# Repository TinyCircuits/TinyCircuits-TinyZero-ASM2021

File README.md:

# TinyCircuits TinyZero Processor Board
# ASM2021 Rev5

These are the design files for the TinyCircuits ASM2021 Rev 5 PCB.  This is a Tiny processor board (Square Version, 20mm x 20mm) that uses the same microcontroller (Atmel ATSAMD21G18A) as the Arduino Zero and has stackable TinyShield support.  

Format is in Cadsoft Eagle format - Eagle version 6.2 was used for the original design.

For more infomation on this, check out the product page at TinyCircuits.com:  https://tinycircuits.com/products/tinyzero-processor

# License:

Design by TinyCircuits.
All design files are released under the Creative Commons Attribution Share-Alike 3.0 License, see the following link for details: http://creativecommons.org/licenses/by-sa/3.0

All text above must be included in any redistribution or derived design

This project uses designs and concepts developed as part of the Arduino project and the LilyPad project.  The TinyCircuits design files themselves (schematics, PCB and libraries) are not directly derived from these works' design files and have been created new, however the concepts and basic architecture behind the TinyDuino and TinyLily products are derived and we thank the hard work of the organizations below for their contributions to open-source hardware:
  
Original Arduino Uno Design by Team Arduino

LilyPad Arduino Design by Leah Buechley and Sparkfun Electronics

Please support the open-source hardware community

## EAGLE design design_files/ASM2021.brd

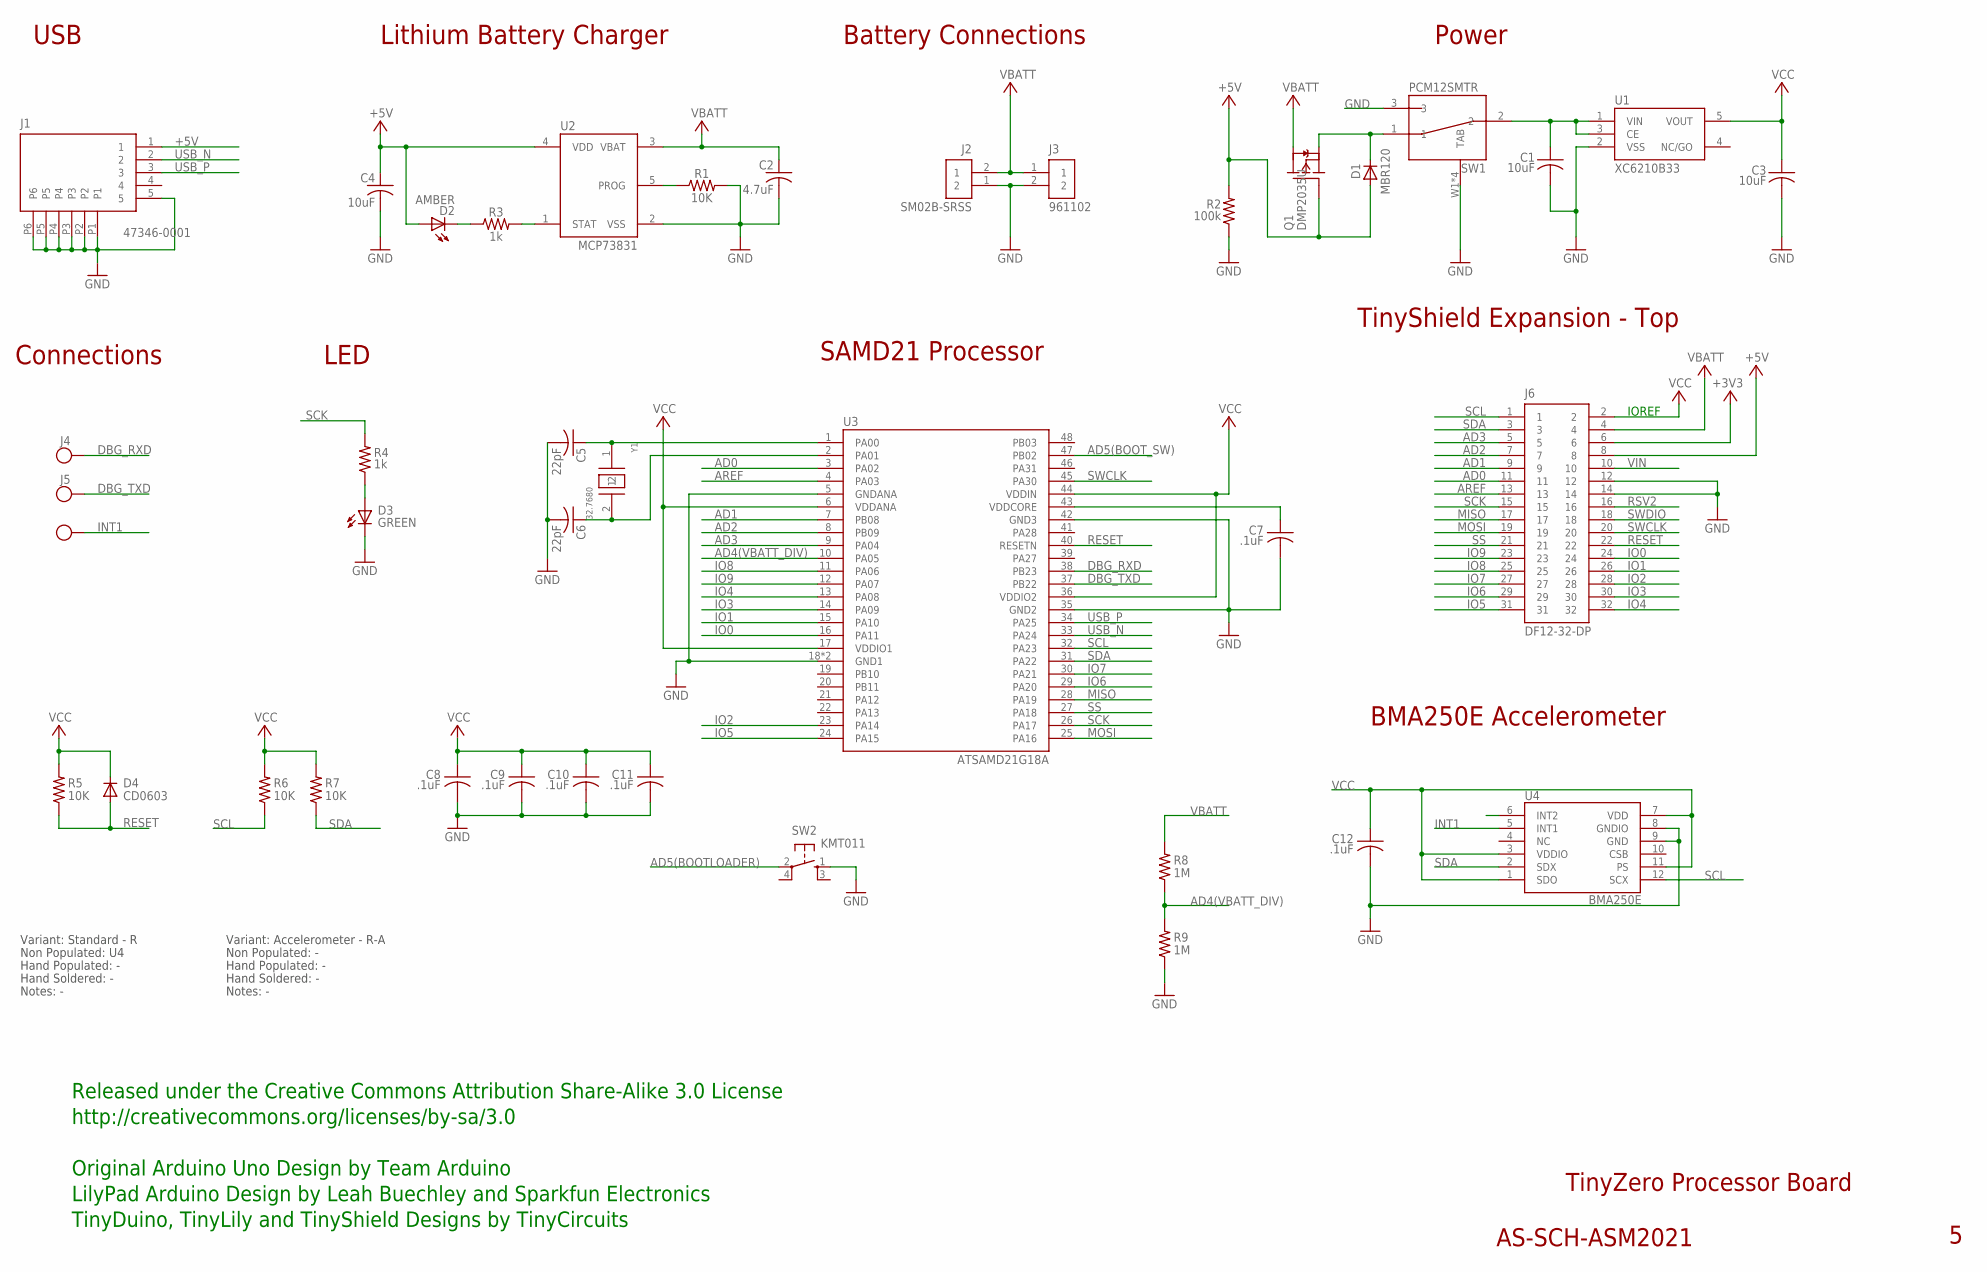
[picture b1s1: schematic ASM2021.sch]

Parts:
C1, C3, C4: 10uF; C0603; PARTNO AS-ITM-00002
C2: 4.7uF; C0603; PARTNO AS-ITM-00088
C5, C6: 22pF; C0402; PARTNO AS-ITM-00211
C7, C8, C9, C10, C11, C12: .1uF; C0402; PARTNO AS-ITM-00008
D1: MBR120; SOD-123FL
D2: AMBER; LNJ_LED; PARTNO AS-ITM-00026
D3: GREEN; LNJ_LED; PARTNO AS-ITM-00011
D4: CD0603; 0603; PARTNO AS-ITM-00009
J1: 47346-0001; MICRO_USB
J2: SM02B-SRSS; JST_SH_2X1
J3: 961102; 2X.1"
J4, J5: TEST_POINT; TEST_POINT_1MM
J6: DF12-32-DP; PARTNO AS-ITM-00015
Q1: DMP2035U; SOT23
R1: 10K; 0402
R2: 100k; 0402; PARTNO AS-ITM-00004
R3, R4: 1k; 0402; PARTNO AS-ITM-00003
R5, R6, R7: 10K; 0402; PARTNO AS-ITM-00032
R8, R9: 1M; 0402; PARTNO AS-ITM-00005
SW1: PCM12SMTR
SW2: KMT011
U1: XC6210B33; SOT-25
U2: MCP73831; SOT-23
U3: ATSAMD21G18A; QFN48; PARTNO AS-ITM-00273
U4: BMA250E; 3-AXIS_ACCELEROMETER
Y1: 32.7680; ABS06; PARTNO AS-ITM-00279

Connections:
+3V3: J6.6
+5V: C4.1, D1.A, D2.A, J1.1, J6.8, Q1.B (G), R2.2, U2.4 (VDD)
AD0: J6.11, U3.3 (PA02)
AD1: J6.9, U3.7 (PB08)
AD2: J6.7, U3.8 (PB09)
AD3: J6.5, U3.9 (PA04)
AD4(VBATT_DIV): R8.1, R9.2, U3.10 (PA05)
AD5(BOOTLOADER): SW2.2
AD5(BOOT_SW): U3.47 (PB02)
AREF: J6.13, U3.4 (PA03)
DBG_RXD: J4.P$1, U3.38 (PB23)
DBG_TXD: J5.P$1, U3.37 (PB22)
GND: C1.2, C2.2, C3.2, C4.2, C5.2, C6.2, C7.2, C8.2, C9.2, C10.2, C11.2, C12.2, D3.C, J1.5, J1.P1, J1.P2, J1.P3, J1.P4, J1.P5, J1.P6, J2.1 (2), J3.2, J6.12, J6.14, R1.2, R2.1, R9.1, SW1.3, SW1.W1 (TAB), SW1.W2 (TAB), SW1.W3 (TAB), SW1.W4 (TAB), SW2.1, U1.2 (VSS), U2.2 (VSS), U3.5 (GNDANA), U3.18 (GND1), U3.35 (GND2), U3.42 (GND3), U3.EXP (GND1), U4.8 (GNDIO), U4.9 (GND)
INT1: U4.5 (INT1)
IO0: J6.24, U3.16 (PA11)
IO1: J6.26, U3.15 (PA10)
IO2: J6.28, U3.23 (PA14)
IO3: J6.30, U3.14 (PA09)
IO4: J6.32, U3.13 (PA08)
IO5: J6.31, U3.24 (PA15)
IO6: J6.29, U3.29 (PA20)
IO7: J6.27, U3.30 (PA21)
IO8: J6.25, U3.11 (PA06)
IO9: J6.23, U3.12 (PA07)
MISO: J6.17, U3.28 (PA19)
MOSI: J6.19, U3.25 (PA16)
unnamed: C5.1, U3.1 (PA00), Y1.1
unnamed: D1.C, Q1.E (S), SW1.1
unnamed: C6.1, U3.2 (PA01), Y1.2
unnamed: D3.A, R4.1
unnamed: D2.C, R3.1
unnamed: R1.1, U2.5 (PROG)
unnamed: R3.2, U2.1 (STAT)
unnamed: C7.1, U3.43 (VDDCORE)
RESET: D4.A, J6.22, R5.1, U3.40 (RESETN)
RSV2: J6.16
SCK: J6.15, R4.2, U3.26 (PA17)
SCL: J6.1, R6.1, U3.32 (PA23), U4.12 (SCX)
SDA: J6.3, R7.1, U3.31 (PA22), U4.2 (SDX)
SS: J6.21, U3.27 (PA18)
SWCLK: J6.20, U3.45 (PA30)
SWDIO: J6.18
USB_N: J1.2, U3.33 (PA24)
USB_P: J1.3, U3.34 (PA25)
VBATT: C2.1, J2.2 (1), J3.1, J6.4, Q1.C (D), R8.2, U2.3 (VBAT)
VCC: C3.1, C8.1, C9.1, C10.1, C11.1, C12.1, D4.C, J6.2, R5.2, R6.2, R7.2, U1.5 (VOUT), U3.6 (VDDANA), U3.17 (VDDIO1), U3.36 (VDDIO2), U3.44 (VDDIN), U4.1 (SDO), U4.3 (VDDIO), U4.7 (VDD), U4.11 (PS)
VCC_IN: C1.1, SW1.2, U1.1 (VIN), U1.3 (CE)
VIN: J6.10

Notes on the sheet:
IOREF
TinyShield Expansion - Top
SAMD21 Processor
Power
LED
TinyZero Processor Board
AS-SCH-ASM2021
Released under the Creative Commons Attribution Share-Alike 3.0 License
http://creativecommons.org/licenses/by-sa/3.0
Original Arduino Uno Design by Team Arduino
TinyDuino, TinyLily and TinyShield Designs by TinyCircuits
LilyPad Arduino Design by Leah Buechley and Sparkfun Electronics
Lithium Battery Charger
Battery Connections
USB
BMA250E Accelerometer
Connections
Non Populated: U4
Hand Populated: -
Hand Soldered: -
Notes: -
Variant: Standard - R
Non Populated: -
Variant: Accelerometer - R-A

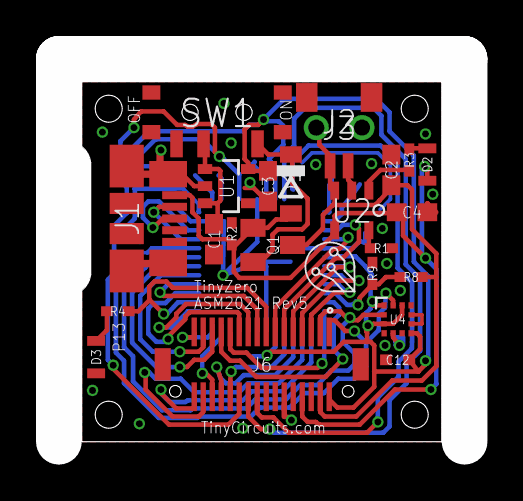
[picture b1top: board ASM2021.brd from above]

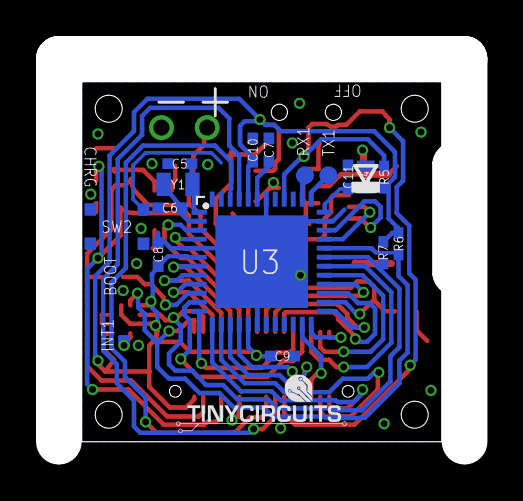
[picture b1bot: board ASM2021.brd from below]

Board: 2 copper layers, 20.0 x 20.0 mm, 40 parts (16 on the bottom side), 41 nets.

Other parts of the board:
U$1: DOCFIELD-TINYCIRCUITS-PCB

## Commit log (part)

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2018-12-31 adding files
2018-12-31 add library submodule
2018-12-31 fix submodule
2018-12-31 add examples
2018-12-31 edit pictures, fix library
2019-01-02 add file
2019-01-10 add tutorial pictures
2019-05-22 added images
2019-07-08 add zip files
2020-01-10 add configuration to library
    add configuration functions for sample rate and measurement scale as well as a rudimentary internal timing so that the library can be polled for a new sample.
2020-02-11 image update
2020-06-26 Add CAD data
2020-06-29 Rename files, add dxf, and use new template for 2D drawings
2020-07-01 Remove vias in models & drawings, add compact dimension images, and remove file to reduce size
2020-07-01 Add STL
2020-07-02 Add zip of all CAD files
2020-08-18 Update CAD drawings
